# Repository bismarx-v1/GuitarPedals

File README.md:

*CUSTOM GUITAR PEDALS*

Custom guitar pedals for playing, started with digital signal processing pedal (DSPP-1) might add more later on, repo contains hardware and software for the pedals. 

Repo also contains music/song recordings

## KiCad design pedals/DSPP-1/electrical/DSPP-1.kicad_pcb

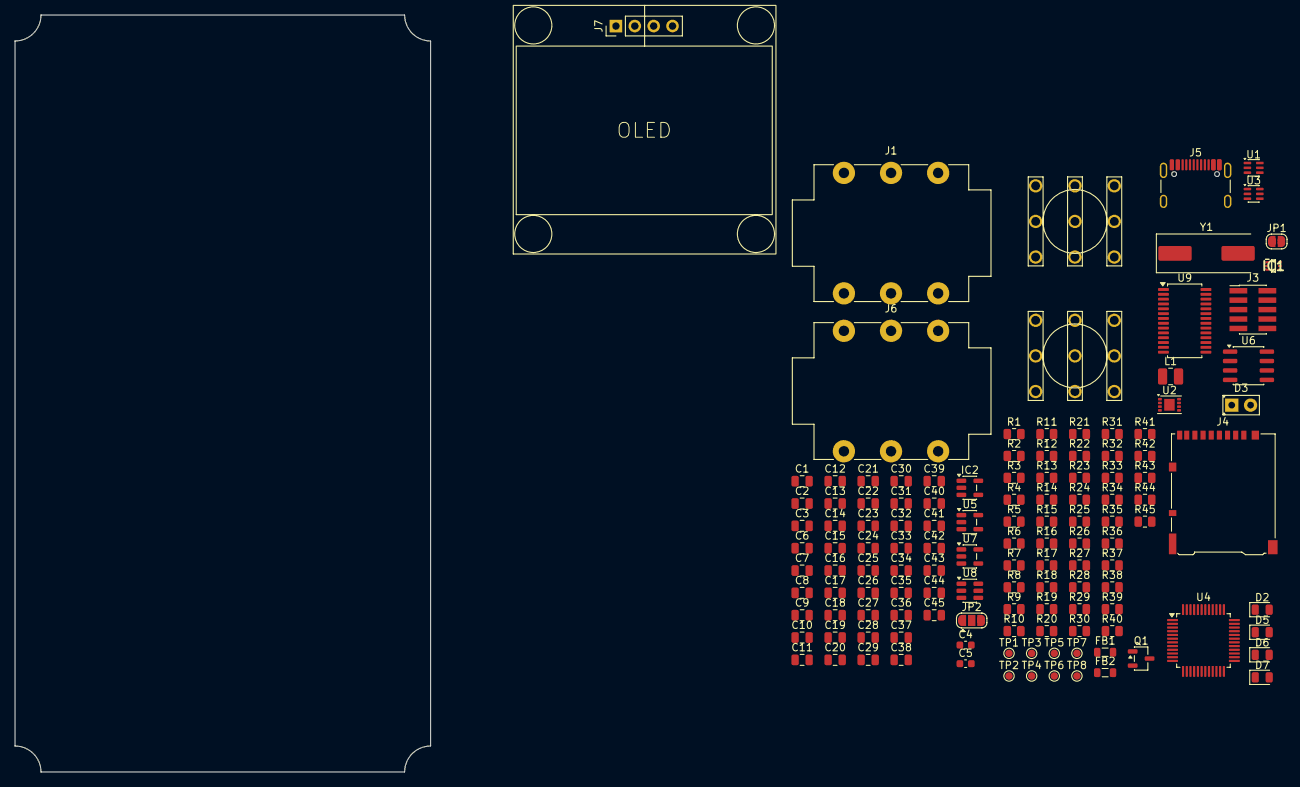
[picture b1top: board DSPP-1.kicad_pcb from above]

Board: 2 copper layers, 56.0 x 102.0 mm, 129 parts (0 on the bottom side), 78 nets, no tracks yet.

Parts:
C1, C2, C12, C14, C15, C16, C17, C21, C23, C27, C28, C36, C39, C40, C43, C45: 10u; C_0805_2012Metric
C3, C6, C8, C9, C10, C11, C13, C18, C19, C20, C22, C25, C29, C30, C31, C34, C37, C38, C41, C42, C44: 100n; C_0805_2012Metric
C4, C5: 30p; C_0603_1608Metric
C7: 100p; C_0805_2012Metric
C24, C26, C32, C33, C35: 22u; C_0805_2012Metric
D2: SD0805S020S0R5; D_0805_2012Metric
D3: LED; LED_D2.0mm_W4.8mm_H2.5mm_FlatTop
D5, D6, D7: LED; LED_0805_2012Metric
FB1, FB2: 742792042; L_0805_2012Metric
IC1: TPS565247DRLR; SOTFL50P160X60-6N
IC2: TLV77333PDBVR; SOT-23-5
J1, J6: Guitar Jack; Jack_6.35mm_Neutrik_NMJ6HCD2_Horizontal
J3: SWD; PinHeader_2x05_P1.27mm_Vertical_SMD
J4: DM3AT; microSD_HC_Hirose_DM3AT-SF-PEJM5
J5: USB_C; USB_C_Receptacle_GCT_USB4105-xx-A_16P_TopMnt_Horizontal
J7: OLED; OLED DISPLAY
JP1: Jumper_2_Small_Open; SolderJumper-2_P1.3mm_Open_RoundedPad1.0x1.5mm
JP2: Jumper; SolderJumper-3_P1.3mm_Open_RoundedPad1.0x1.5mm
L1: 2.2u; L_1008_2520Metric
Q1: SI2393DS; SOT-23-3
R1, R13, R20, R23, R26, R27, R28, R29, R30, R34, R35, R40, R41: 10k; R_0805_2012Metric
R2, R3, R4, R5, R6, R14, R15, R16, R17, R18, R33: 22R; R_0805_2012Metric
R7: 2.2M; R_0805_2012Metric
R8, R31, R32, R43, R44, R45: 2.2k; R_0805_2012Metric
R9: 1M; R_0805_2012Metric
R10: 1k; R_0805_2012Metric
R11, R12, R19, R24, R25: 100k; R_0805_2012Metric
R21: 100R; R_0805_2012Metric
R22: 76.8k; R_0805_2012Metric
R36, R39: 5.1k; R_0805_2012Metric
R37, R38: 15R; R_0805_2012Metric
R42: 0/220k; R_0805_2012Metric
SW1: SW_3PDT; STOMP-SWITCH-3PDT
SW5: FOOTSW_3PDT; STOMP-SWITCH-3PDT
TP1, TP2, TP3, TP4, TP5, TP6, TP7, TP8: TestPoint; TestPoint_Pad_D1.0mm
U1, U3: LM66100DCKR; SOT-363_SC-70-6
U2: OPA1678; SON-8-1EP_3x2mm_P0.5mm_EP1.4x1.6mm
U4: STM32G474CBT6TR; LQFP-48_7x7mm_P0.5mm
U5: TPS7A2055PDBVRG4; SOT-23-5
U6: APS6404L-3SQRx-SN; SOIC-8_3.9x4.9mm_P1.27mm
U7: 24CW1280T-I/OT; SOT-23-5
U8: USBLC6-2SC6; SOT-23-6
U9: PCM3060; TSSOP-28_4.4x9.7mm_P0.65mm
Y1: ABLS-12.288; Crystal_SMD_HC49-SD

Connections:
+3V3: C1.2, C3.2, C6.2, C8.2, C10.2, C27.2, C28.2, C29.2, C30.2, C34.2, C36.2, C37.2, C40.2, C41.2, FB1.1, IC2.5 (OUT), J3.1, J4.4 (VDD), JP1.2 (B), JP2.3 (B), R1.1, R8.1, R20.1, R27.2, R28.1, R30.2, R31.1, R32.1, R34.2, R35.2, R41.2, R45.1, U4.1 (VBAT), U4.24 (VDD), U4.36 (VDD), U4.48 (VDD), U6.8 (VDD), U7.4 (V_{CC}), U9.7 (V_{DD})
+5V2: C2.2, C31.1, C32.1, C33.1, C35.1, L1.2, R22.2, U1.1 (VIN), U3.3 (~CE)
+5VA: C11.2, C20.2, C21.2, C42.2, C43.2, R11.1, R44.1, U2.8 (V+), U5.5 (OUT), U9.24 (V_{CC})
/AUDIO_BIAS: R9.1, U2.1, U2.2 (-)
/BOOT0: R26.1, U4.45 (PB8)
/D+: U4.34 (PA12), U8.4 (I/O2)
/D-: U4.33 (PA11), U8.6 (I/O1)
/DN_IN: R37.2, U8.1 (I/O1)
/DP_IN: R38.2, U8.3 (I/O2)
/FOOTSW_IO: R30.1, SW5.5 (B)
/NRST: C19.2, J3.10, R27.1, U4.7 (PG10)
/OUTPUT_AUDIO: J6.T, SW5.2 (B)
/QSPI_CLK: R4.1, U6.6 (SCLK)
/QSPI_CS: R35.1, U4.10 (PA2), U6.1 (~CE)
/QSPI_IO0: R3.1, U6.5 (SI/SIO0)
/QSPI_IO1: R2.1, U6.2 (SO/SIO1)
/QSPI_IO2: R16.2, U6.3 (SIO2)
/QSPI_IO3: R15.2, U6.7 (SIO3)
/SAI_FS_A: R18.2, U9.4 (LRCK1), U9.11 (LRCK2)
/SAI_MCLK_A: R14.2, U9.6 (SCKI1), U9.9 (SCKI2)
/SAI_SCK_A: R17.2, U9.5 (BCK1), U9.10 (BCK2)
/SAI_SD_A: U4.32 (PA10), U9.12 (DIN)
/SAI_SD_B: U4.42 (PB5), U9.3 (DOUT)
/SCL: R20.2, U4.39 (PA15), U7.1 (SCL), U9.1 (MC/SCL/FMT)
/SDA: R1.2, U4.44 (PB7), U7.3 (SDA), U9.2 (MD/SDA/DEMP)
/SPI_CLK: J4.5 (CLK), R5.1
/SPI_CS: J4.2 (DAT3/CD), R34.1, U4.26 (PB12)
/SPI_MISO: R33.1, U4.28 (PB14)
/SPI_MOSI: J4.3 (CMD), R6.1
/SWCLK: J3.4, R29.1, U4.38 (PA14)
/SWDIO: J3.2, R28.2, U4.37 (PA13)
/SWO: J3.6, U4.40 (PB3)
/VDDA: C13.2, C14.2, FB1.2, U4.20 (VREF+), U4.21 (VDDA)
GND: C1.1, C2.1, C3.1, C4.2, C5.2, C6.1, C7.1, C8.1, C10.1, C11.1, C12.1, C13.1, C14.1, C16.2, C17.1, C18.1, C19.1, C20.1, C21.1, C22.2, C23.1, C24.2, C25.1, C26.2, C27.1, C28.1, C29.1, C30.1, C31.2, C32.2, C33.2, C34.1, C35.2, C36.1, C37.1, C38.2, C39.1, C40.1, C41.1, C42.1, C43.1, C44.1, C45.1, D5.1 (K), D6.1 (K), D7.1 (K), IC1.3 (GND), IC1.4 (AGND), IC2.2 (GND), J1.S, J3.3, J3.5, J3.9, J4.6 (VSS), J4.9 (DET_B), J4.SH (SHIELD), J5.A1 (GND), J5.A12 (GND), J5.B1 (GND), J5.B12 (GND), J5.S1 (SHIELD), J6.S, JP2.1 (A), R7.1, R12.2, R19.1, R23.1, R25.1, R29.2, R36.1, R39.1, R40.1, SW1.1 (A), SW1.6 (C), SW1.8 (B), SW5.6 (C), SW5.9 (C), U1.2 (GND), U2.4 (V-), U3.2 (GND), U4.19 (VSSA), U4.23 (VSS), U4.35 (VSS), U4.47 (VSS), U5.2 (GND), U6.4 (VSS), U7.2 (V_{SS}), U8.2 (GND), U9.8 (DGND), U9.22 (AGND2), U9.23 (AGND1)
unnamed: C7.2, C9.1, J1.T, R7.2
unnamed: C9.2, R9.2, R10.1
unnamed: C15.2, R19.2, R21.1
unnamed: D2.2 (A), SW1.3 (C), SW1.4 (A)
unnamed: D3.2 (A), R31.2
unnamed: D3.1 (K), SW5.8 (B)
unnamed: D5.2 (A), R43.2
unnamed: D6.2 (A), R44.2
unnamed: D7.2 (A), R45.2
unnamed: IC1.5 (EN), R24.1, R25.2
unnamed: IC1.6 (FB), R22.1, R23.2
unnamed: IC1.2 (SW), L1.1
unnamed: J4.7 (DAT0), R33.2
unnamed: J5.A5 (CC1), R39.2
unnamed: J5.B5 (CC2), R36.2
unnamed: J5.A6 (D+), J5.B6 (D+), R38.1
unnamed: J5.A7 (D-), J5.B7 (D-), R37.1
unnamed: JP1.1 (A), R40.2, U9.27 (~MS/AD/IFMD)
unnamed: JP2.2 (C), R42.1
unnamed: Q1.1 (G), R13.1
unnamed: C16.1, R11.2, R12.1, U2.3 (+)
unnamed: R10.2, U2.5 (+)
unnamed: C15.1, U2.6 (-), U2.7
unnamed: R14.1, U4.11 (PA3)
unnamed: R15.1, U4.14 (PA6)
unnamed: R16.1, U4.15 (PA7)
unnamed: R17.1, U4.30 (PA8)
unnamed: R18.1, U4.31 (PA9)
unnamed: R2.2, U4.16 (PB0)
unnamed: R3.2, U4.17 (PB1)
unnamed: R4.2, U4.22 (PB10)
unnamed: R5.2, U4.27 (PB13)
unnamed: R6.2, U4.29 (PB15)
unnamed: C4.1, U4.5 (PF0), Y1.1
unnamed: C5.1, U4.6 (PF1), Y1.2
unnamed: C17.2, C18.2, FB2.2, U5.1 (IN), U5.3 (EN)
unnamed: R42.2, U9.28 (MODE)
unnamed: C44.2, C45.2, U9.21 (V_{COM})
unnamed: C39.2, U9.26 (V_{IN}R)
unnamed: R41.1, U9.15 (~RST)
USB_VBUS: C12.2, C38.1, J5.A4 (VBUS), J5.A9 (VBUS), J5.B4 (VBUS), J5.B9 (VBUS), R43.1, TP5.1 (1_1), U1.3 (~CE), U3.1 (VIN), U8.5 (VBUS)
VCC: C23.2, C25.2, FB2.1, IC2.1 (IN), IC2.3 (EN), U1.6 (VOUT), U3.6 (VOUT)
VIN: D2.1 (K), Q1.2 (S), R13.2
VSYS: C22.1, C24.1, C26.1, IC1.1 (VIN), Q1.3 (D), R24.2, TP1.1 (1_1)
